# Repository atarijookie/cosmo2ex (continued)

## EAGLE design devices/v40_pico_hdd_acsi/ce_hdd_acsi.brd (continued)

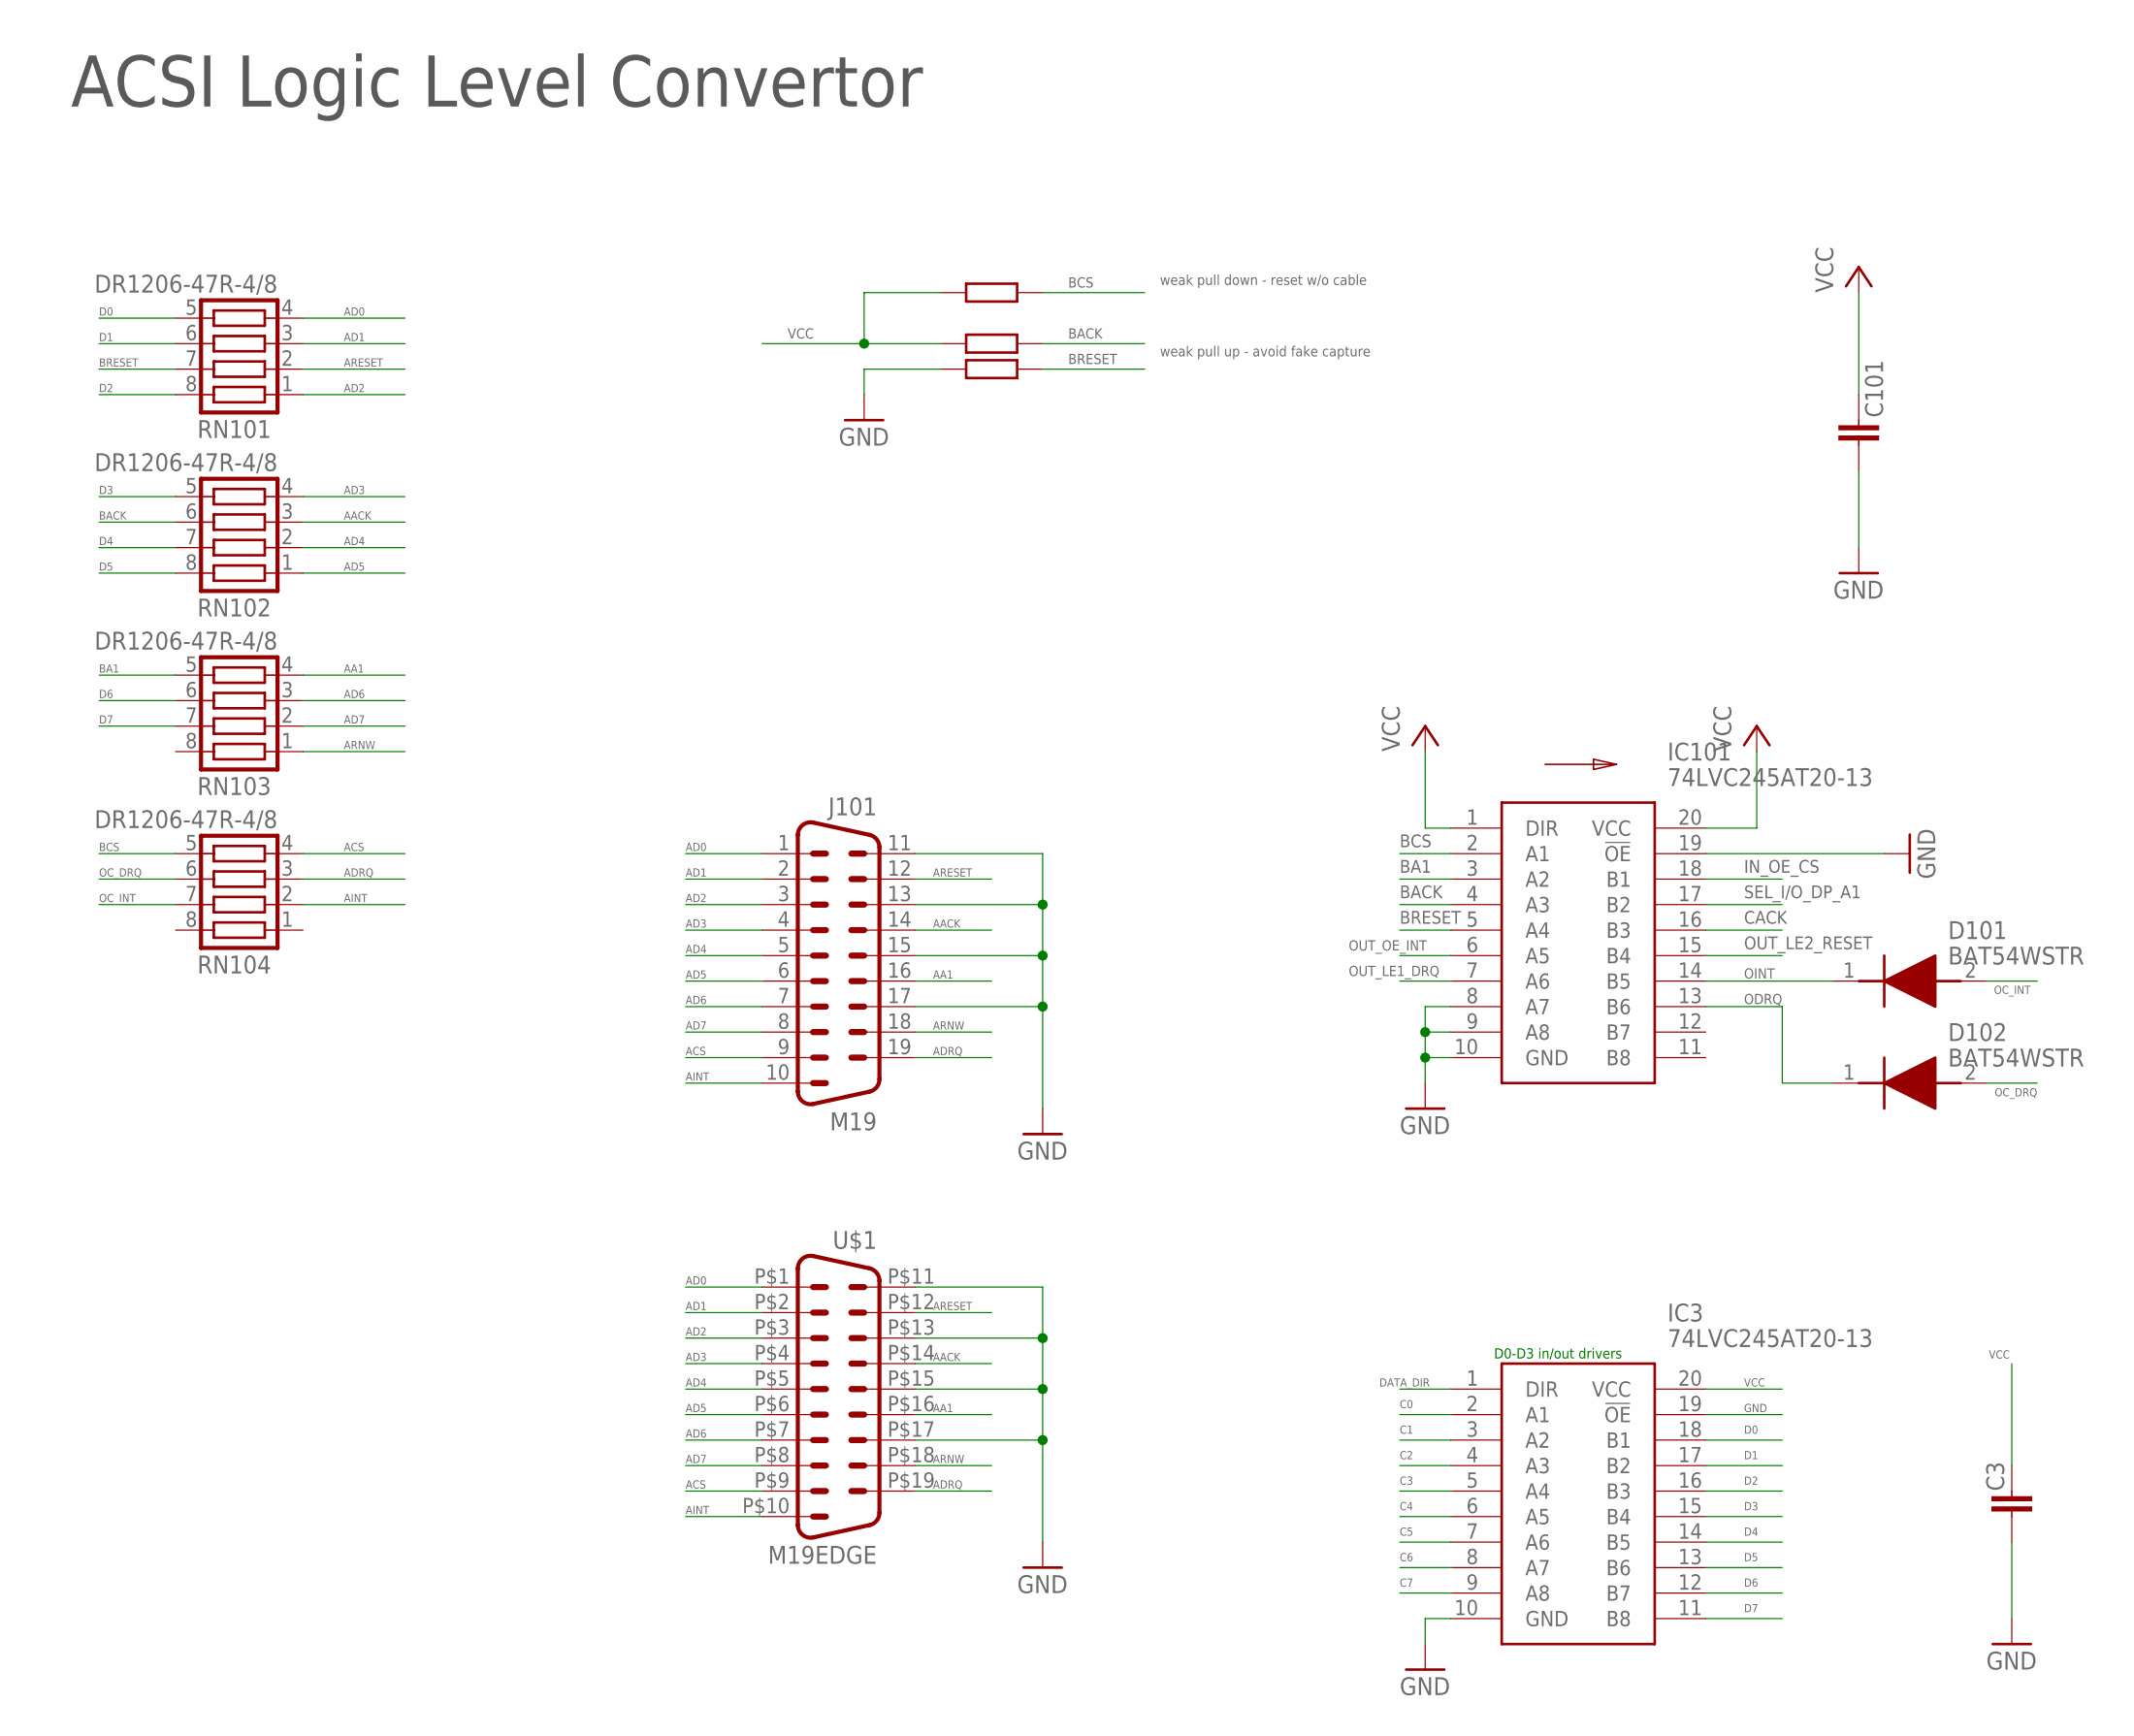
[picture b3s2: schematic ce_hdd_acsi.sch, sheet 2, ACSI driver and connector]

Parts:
C3: 100 nF; C0603
C101: 1 uF; C0603
D101: BAT54WSTR; SOD2613X100N
D102: BAT54WSTR; SOD2613X100N; MANUFACTURER_PART_NUMBER BAT54WSTR
IC3, IC101: 74LVC245AT20-13; SOP65P640X120-20N
J101: M19
R102, R103, R104: 10k; R0603
RN101, RN102, RN103, RN104: DR1206-47R-4/8; CTS742C083
U$1: M19EDGE; M19_EDGE

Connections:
AA1: J101.16, RN103.4, U$1.P$16 (16)
AACK: J101.14, RN102.3, U$1.P$14 (14)
ACS: J101.9, RN104.4, U$1.P$9 (9)
AD0: J101.1, RN101.4, U$1.P$1 (1)
AD1: J101.2, RN101.3, U$1.P$2 (2)
AD2: J101.3, RN101.1, U$1.P$3 (3)
AD3: J101.4, RN102.4, U$1.P$4 (4)
AD4: J101.5, RN102.2, U$1.P$5 (5)
AD5: J101.6, RN102.1, U$1.P$6 (6)
AD6: J101.7, RN103.3, U$1.P$7 (7)
AD7: J101.8, RN103.2, U$1.P$8 (8)
ADRQ: J101.19, RN104.3, U$1.P$19 (19)
AINT: J101.10, RN104.2, U$1.P$10 (10)
ARESET: J101.12, RN101.2, U$1.P$12 (12)
ARNW: J101.18, RN103.1, U$1.P$18 (18)
BA1: IC101.3 (A2), RN103.5
BACK: IC101.4 (A3), R103.2, RN102.6
BCS: IC101.2 (A1), R102.2, RN104.5
BRESET: IC101.5 (A4), R104.2, RN101.7
C0: IC3.2 (A1); also elsewhere on the board
C1: IC3.3 (A2); also elsewhere on the board
C2: IC3.4 (A3); also elsewhere on the board
C3: IC3.5 (A4); also elsewhere on the board
C4: IC3.6 (A5); also elsewhere on the board
C5: IC3.7 (A6); also elsewhere on the board
C6: IC3.8 (A7); also elsewhere on the board
C7: IC3.9 (A8); also elsewhere on the board
CACK: IC101.16 (B3); also elsewhere on the board
D0: IC3.18 (B1), RN101.5
D1: IC3.17 (B2), RN101.6
D2: IC3.16 (B3), RN101.8
D3: IC3.15 (B4), RN102.5
D4: IC3.14 (B5), RN102.7
D5: IC3.13 (B6), RN102.8
D6: IC3.12 (B7), RN103.6
D7: IC3.11 (B8), RN103.7
DATA_DIR: IC3.1 (DIR); also elsewhere on the board
GND: C3.2, C101.2, IC3.10 (GND), IC3.19 (!OE), IC101.8 (A7), IC101.9 (A8), IC101.10 (GND), IC101.19 (!OE), J101.11, J101.13, J101.15, J101.17, R104.1, U$1.P$11 (11), U$1.P$13 (13), U$1.P$15 (15), U$1.P$17 (17); also elsewhere on the board
IN_OE_CS: IC101.18 (B1); also elsewhere on the board
OC_DRQ: D102.2 (A), RN104.6
OC_INT: D101.2 (A), RN104.7
ODRQ: D102.1 (K), IC101.13 (B6)
OINT: D101.1 (K), IC101.14 (B5)
OUT_LE1_DRQ: IC101.7 (A6); also elsewhere on the board
OUT_LE2_RESET: IC101.15 (B4); also elsewhere on the board
OUT_OE_INT: IC101.6 (A5); also elsewhere on the board
SEL_I/O_DP_A1: IC101.17 (B2); also elsewhere on the board
VCC: C3.1, C101.1, IC3.20 (VCC), IC101.1 (DIR), IC101.20 (VCC), R102.1, R103.1; also elsewhere on the board

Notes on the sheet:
ACSI Logic Level Convertor
weak pull down - reset w/o cable
weak pull up - avoid fake capture
D0-D3 in/out drivers

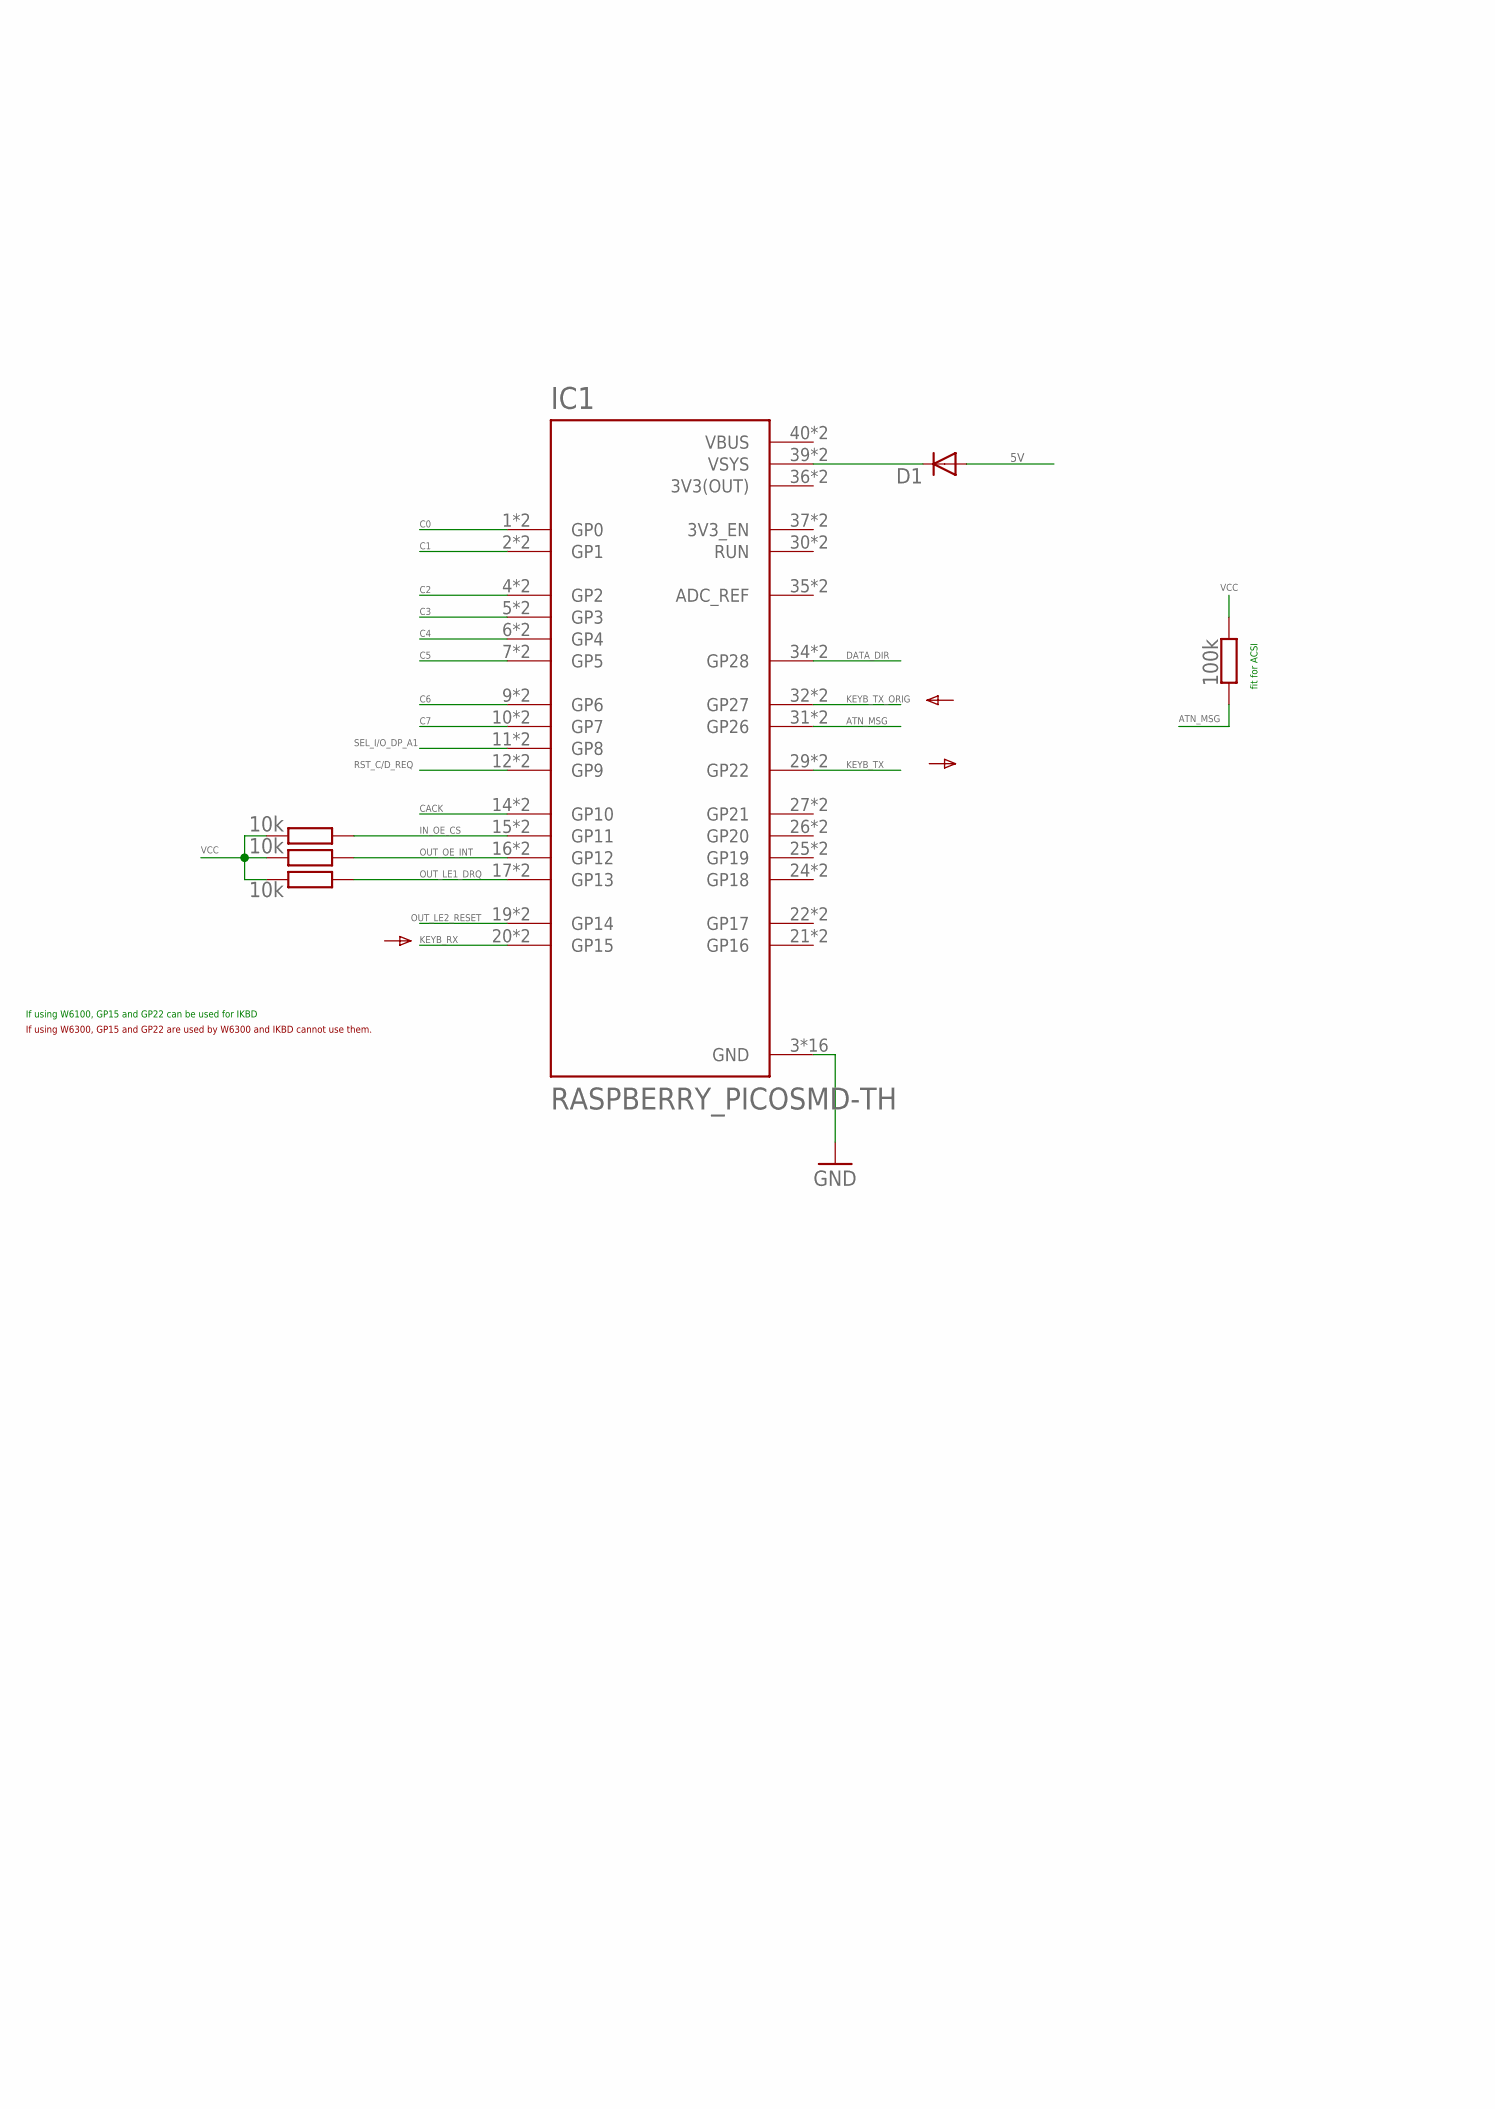
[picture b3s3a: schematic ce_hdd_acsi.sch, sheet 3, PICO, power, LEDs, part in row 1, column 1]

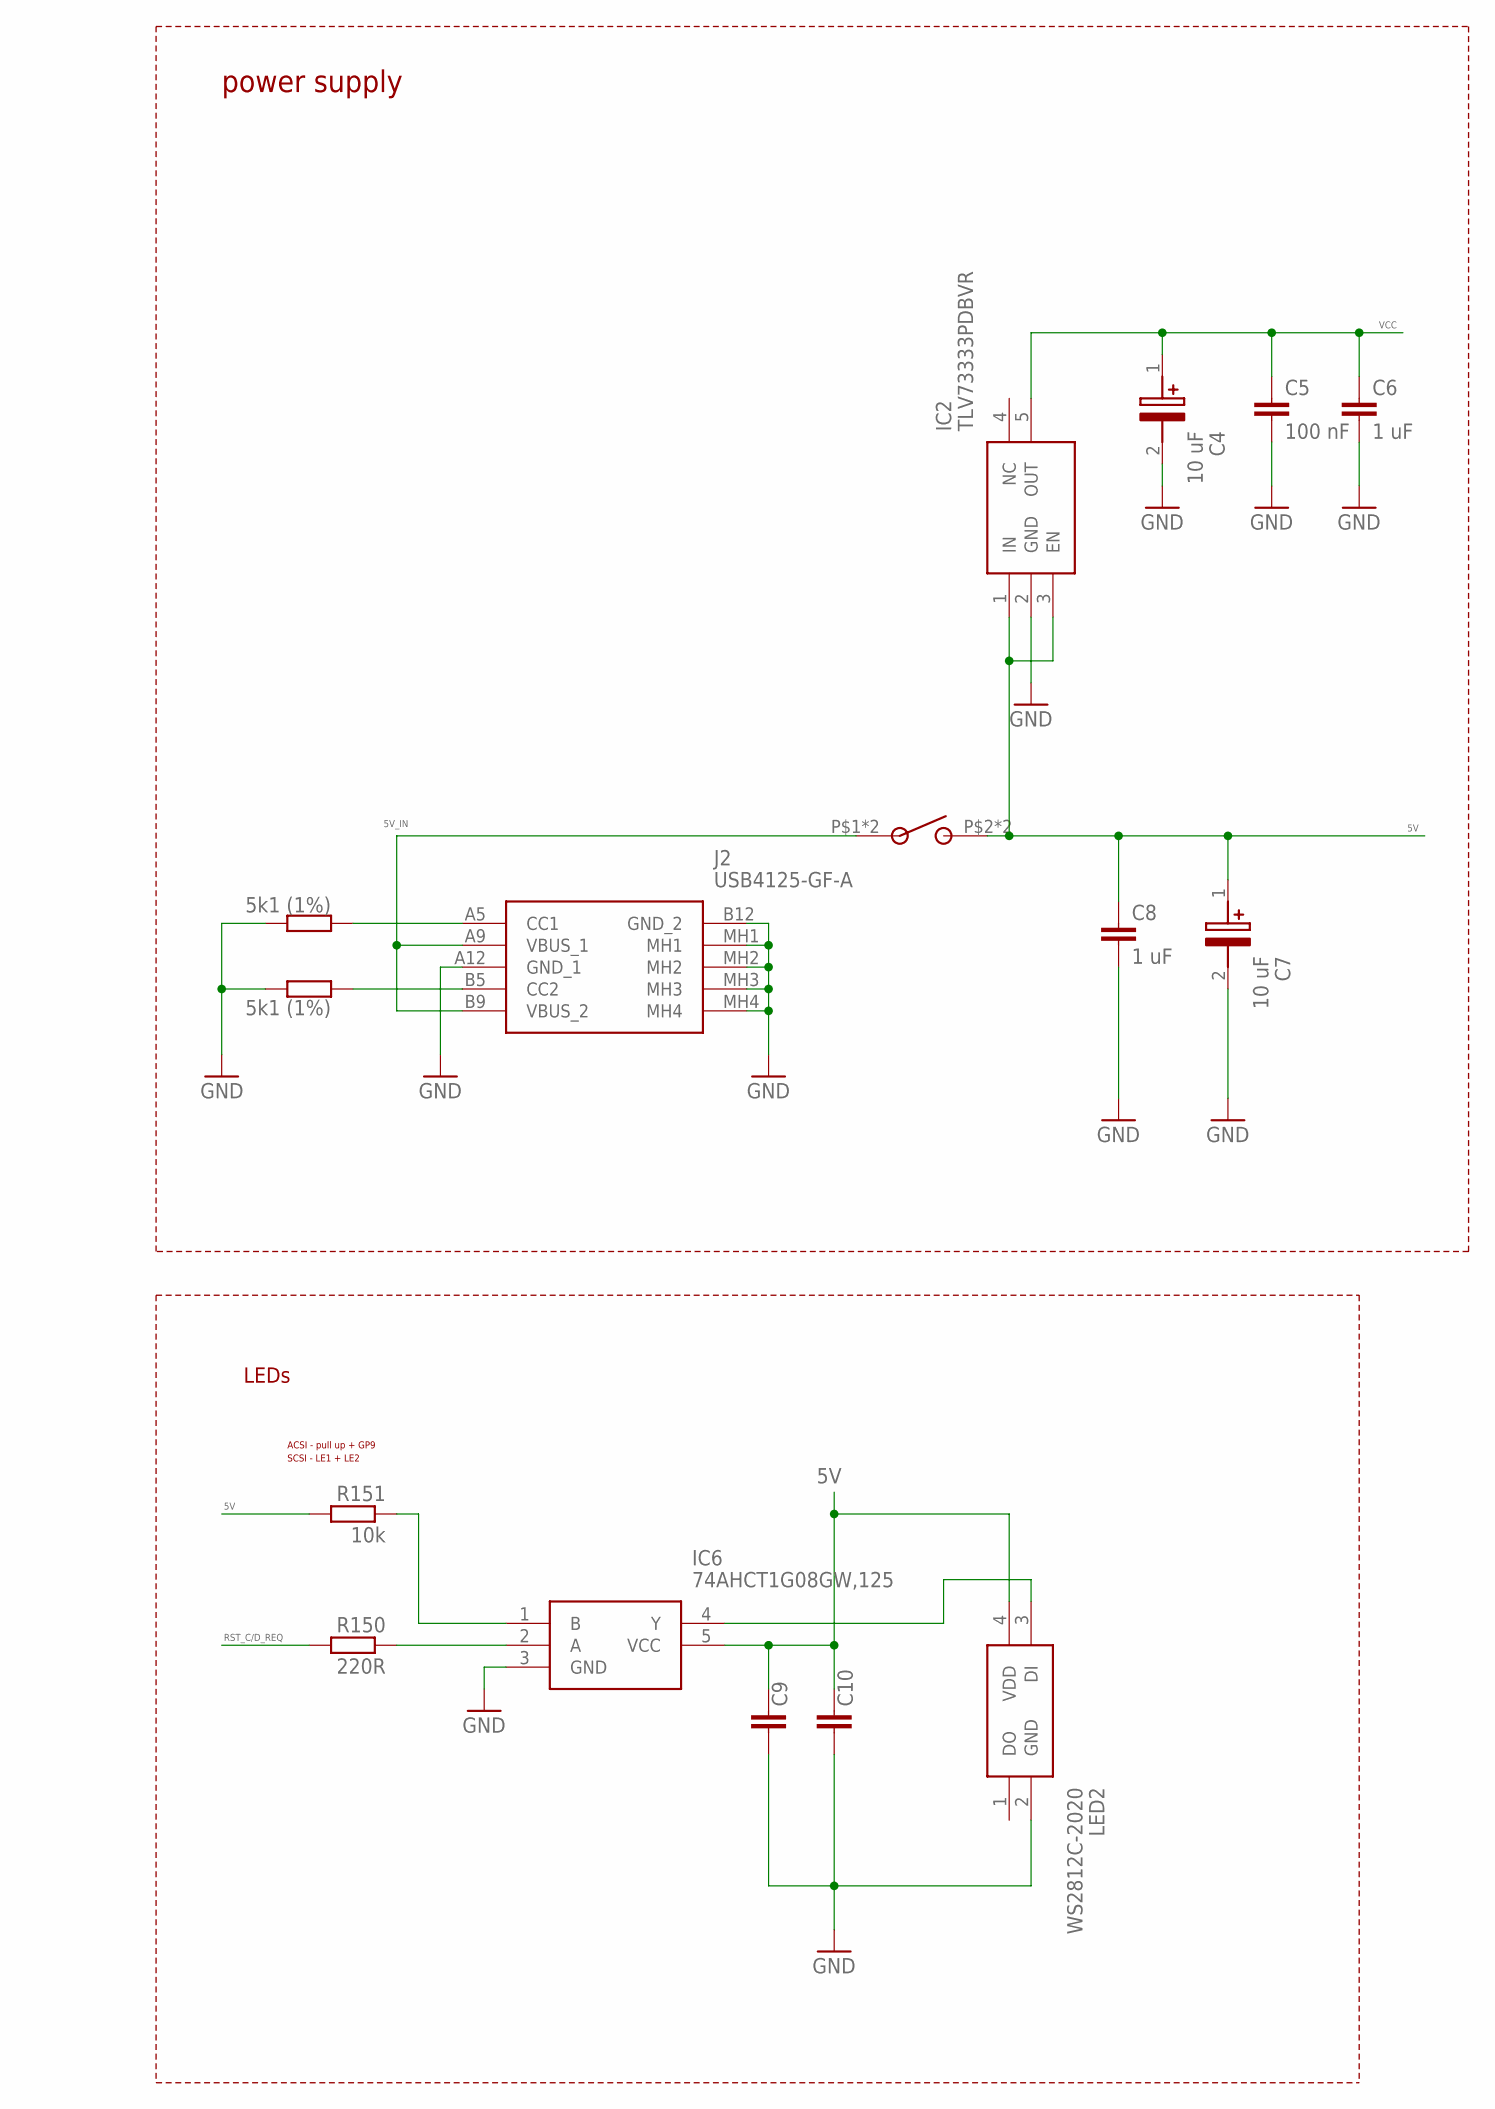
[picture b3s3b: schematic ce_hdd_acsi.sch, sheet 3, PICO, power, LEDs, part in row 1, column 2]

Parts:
C4: 10 uF; CAPPM3528X210N; MANUFACTURER_PART_NUMBER 293D106X9016B2TE3
C5, C9, C10: 100 nF; C0603
C6, C8: 1 uF; C0603
C7: 10 uF; CAPPM3528X210N
D1: SK110-DIO; DO214AC
IC1: RASPBERRY_PICOSMD-TH; PICO-PKG
IC2: TLV73333PDBVR; SOT95P280X145-5N
IC6: 74AHCT1G08GW,125; SOT65P212X110-5N
J2: USB4125-GF-A; USB4125GFA
LED2: WS2812C-2020; WS2812C2020
R3, R4: 5k1 (1%); R0603
R6, R7, R8, R151: 10k; R0603
R125: 100k; R0603
R150: 220R; R0603
SW1: SMSR-1; SMRS-1

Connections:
3V3(OUT): IC1.36 (3V3(OUT)), IC1.P$36 (3V3(OUT))
5V: C7.1 (+), C8.1, C9.1, C10.1, D1.A, IC2.1 (IN), IC2.3 (EN), IC6.5 (VCC), LED2.4 (VDD), R151.2, SW1.P$2, SW1.P$3; also elsewhere on the board
5V_IN: J2.A9 (VBUS_1), J2.B9 (VBUS_2), SW1.P$1, SW1.P$4
ATN_MSG: IC1.31 (GP26), IC1.P$31 (GP26), R125.2
C0: IC1.1 (GP0), IC1.P$1 (GP0); also elsewhere on the board
C1: IC1.2 (GP1), IC1.P$2 (GP1); also elsewhere on the board
C2: IC1.4 (GP2), IC1.P$4 (GP2); also elsewhere on the board
C3: IC1.5 (GP3), IC1.P$5 (GP3); also elsewhere on the board
C4: IC1.6 (GP4), IC1.P$6 (GP4); also elsewhere on the board
C5: IC1.7 (GP5), IC1.P$7 (GP5); also elsewhere on the board
C6: IC1.9 (GP6), IC1.P$9 (GP6); also elsewhere on the board
C7: IC1.10 (GP7), IC1.P$10 (GP7); also elsewhere on the board
CACK: IC1.14 (GP10), IC1.P$14 (GP10); also elsewhere on the board
DATA_DIR: IC1.34 (GP28), IC1.P$34 (GP28); also elsewhere on the board
GND: C4.2 (-), C5.2, C6.2, C7.2 (-), C8.2, C9.2, C10.2, IC1.3 (GND), IC1.8 (GND), IC1.13 (GND), IC1.18 (GND), IC1.23 (GND), IC1.28 (GND), IC1.33 (GND), IC1.38 (GND), IC1.P$3 (GND), IC1.P$8 (GND), IC1.P$13 (GND), IC1.P$18 (GND), IC1.P$23 (GND), IC1.P$28 (GND), IC1.P$33 (GND), IC1.P$38 (GND), IC2.2 (GND), IC6.3 (GND), J2.A12 (GND_1), J2.B12 (GND_2), J2.MH1, J2.MH2, J2.MH3, J2.MH4, LED2.2 (GND), R3.2, R4.2; also elsewhere on the board
IN_OE_CS: IC1.15 (GP11), IC1.P$15 (GP11), R6.2; also elsewhere on the board
KEYB_RX: IC1.20 (GP15), IC1.P$20 (GP15); also elsewhere on the board
KEYB_TX: IC1.29 (GP22), IC1.P$29 (GP22); also elsewhere on the board
KEYB_TX_ORIG: IC1.32 (GP27), IC1.P$32 (GP27); also elsewhere on the board
unnamed: J2.B5 (CC2), R4.1
unnamed: J2.A5 (CC1), R3.1
unnamed: IC6.2 (A), R150.1
unnamed: IC6.1 (B), R151.1
unnamed: IC6.4 (Y), LED2.3 (DI)
unnamed: D1.C, IC1.39 (VSYS), IC1.P$39 (VSYS)
OUT_LE1_DRQ: IC1.17 (GP13), IC1.P$17 (GP13), R8.2; also elsewhere on the board
OUT_LE2_RESET: IC1.19 (GP14), IC1.P$19 (GP14); also elsewhere on the board
OUT_OE_INT: IC1.16 (GP12), IC1.P$16 (GP12), R7.2; also elsewhere on the board
RST_C/D_REQ: IC1.12 (GP9), IC1.P$12 (GP9), R150.2
SEL_I/O_DP_A1: IC1.11 (GP8), IC1.P$11 (GP8); also elsewhere on the board
VBUS: IC1.40 (VBUS), IC1.P$40 (VBUS)
VCC: C4.1 (+), C5.1, C6.1, IC2.5 (OUT), R6.1, R7.1, R8.1, R125.1; also elsewhere on the board

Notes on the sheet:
power supply
If using W6100, GP15 and GP22 can be used for IKBD
If using W6300, GP15 and GP22 are used by W6300 and IKBD cannot use them.
fit for ACSI
LEDs
ACSI - pull up + GP9
SCSI - LE1 + LE2

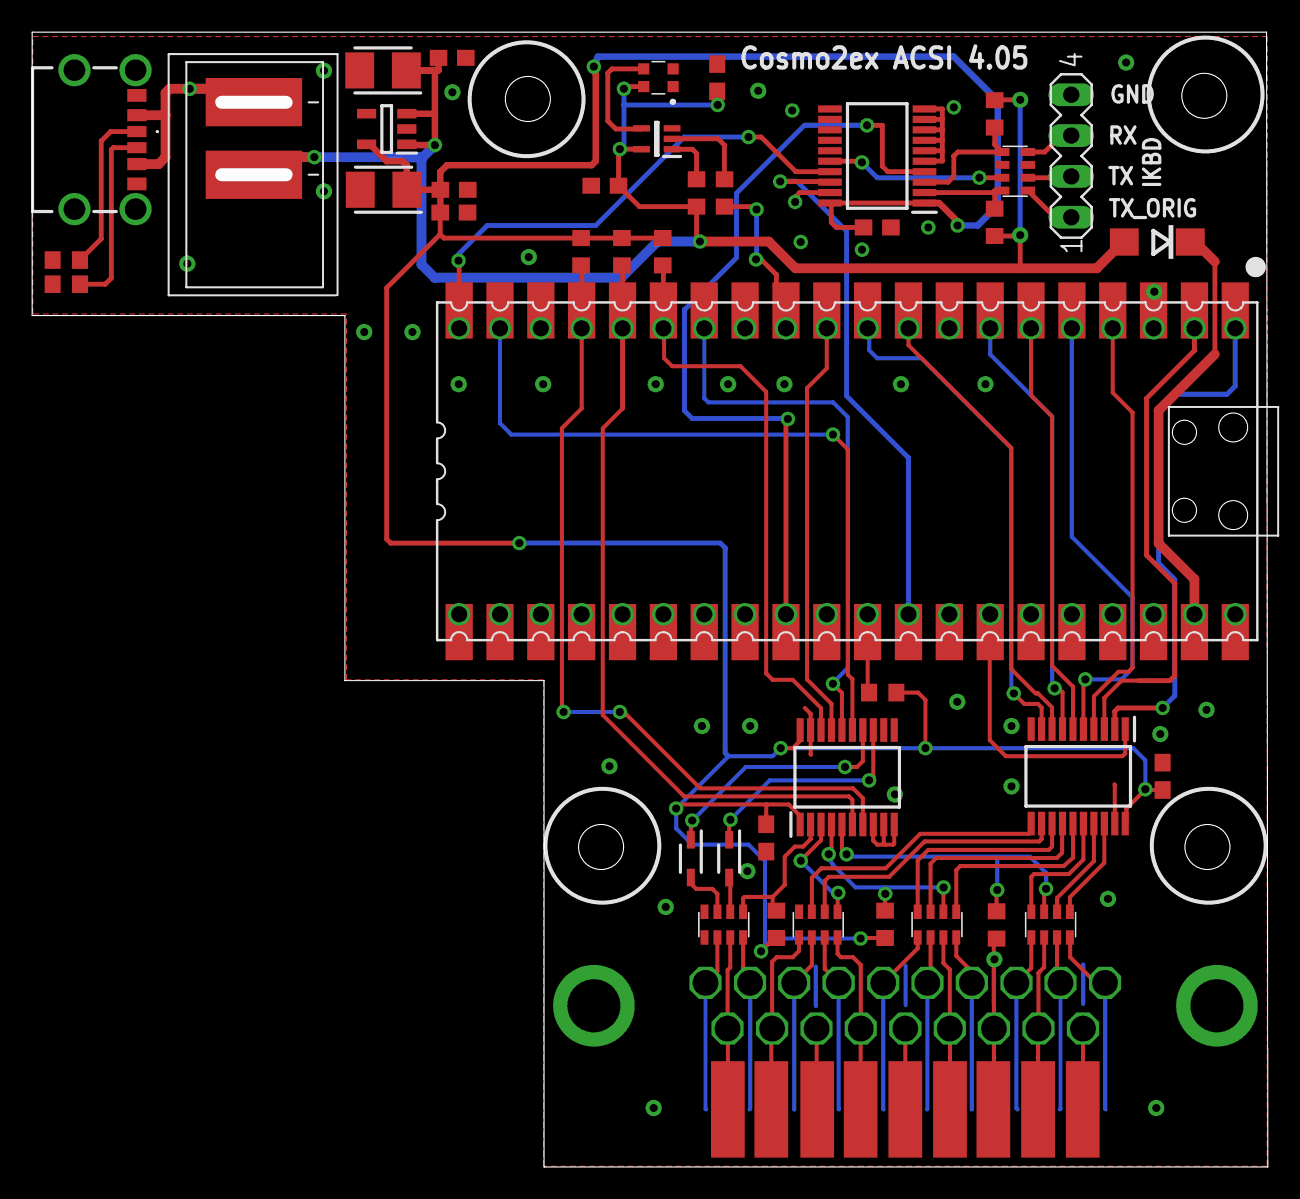
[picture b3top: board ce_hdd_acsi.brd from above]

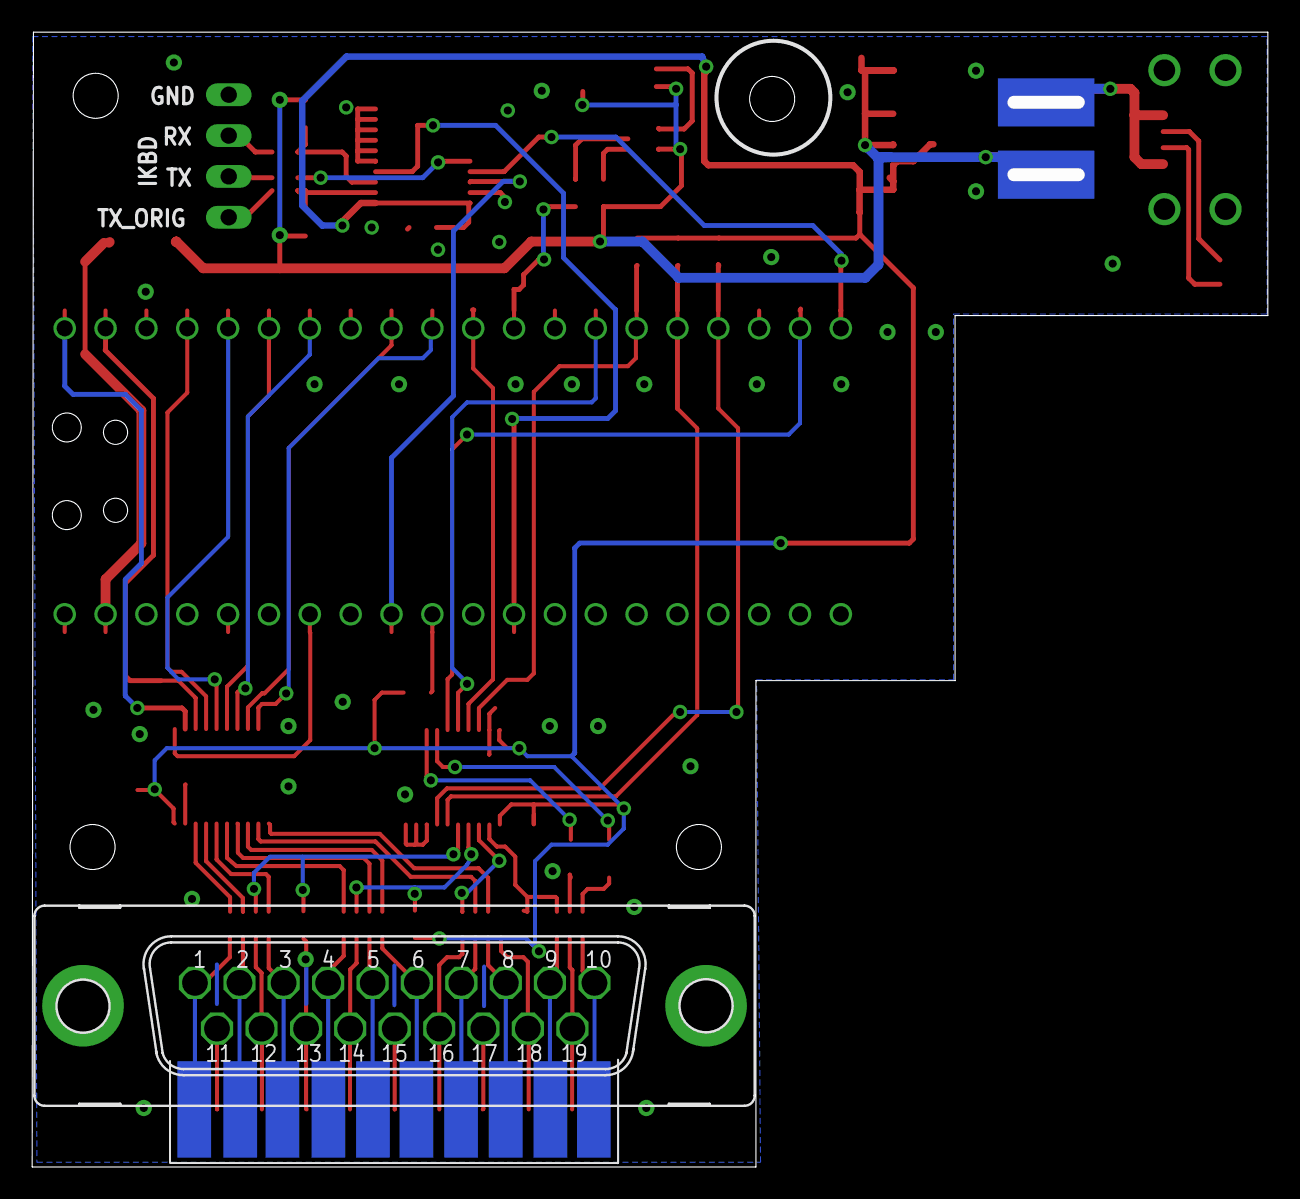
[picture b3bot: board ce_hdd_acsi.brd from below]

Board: 2 copper layers, 76.8 x 70.6 mm, 43 parts (2 on the bottom side), 69 nets.
